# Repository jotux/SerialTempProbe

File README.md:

# SerialTempProbe
Serial temperature probe with 5 channels, K-Type thermocouples, and stm32l4 controller

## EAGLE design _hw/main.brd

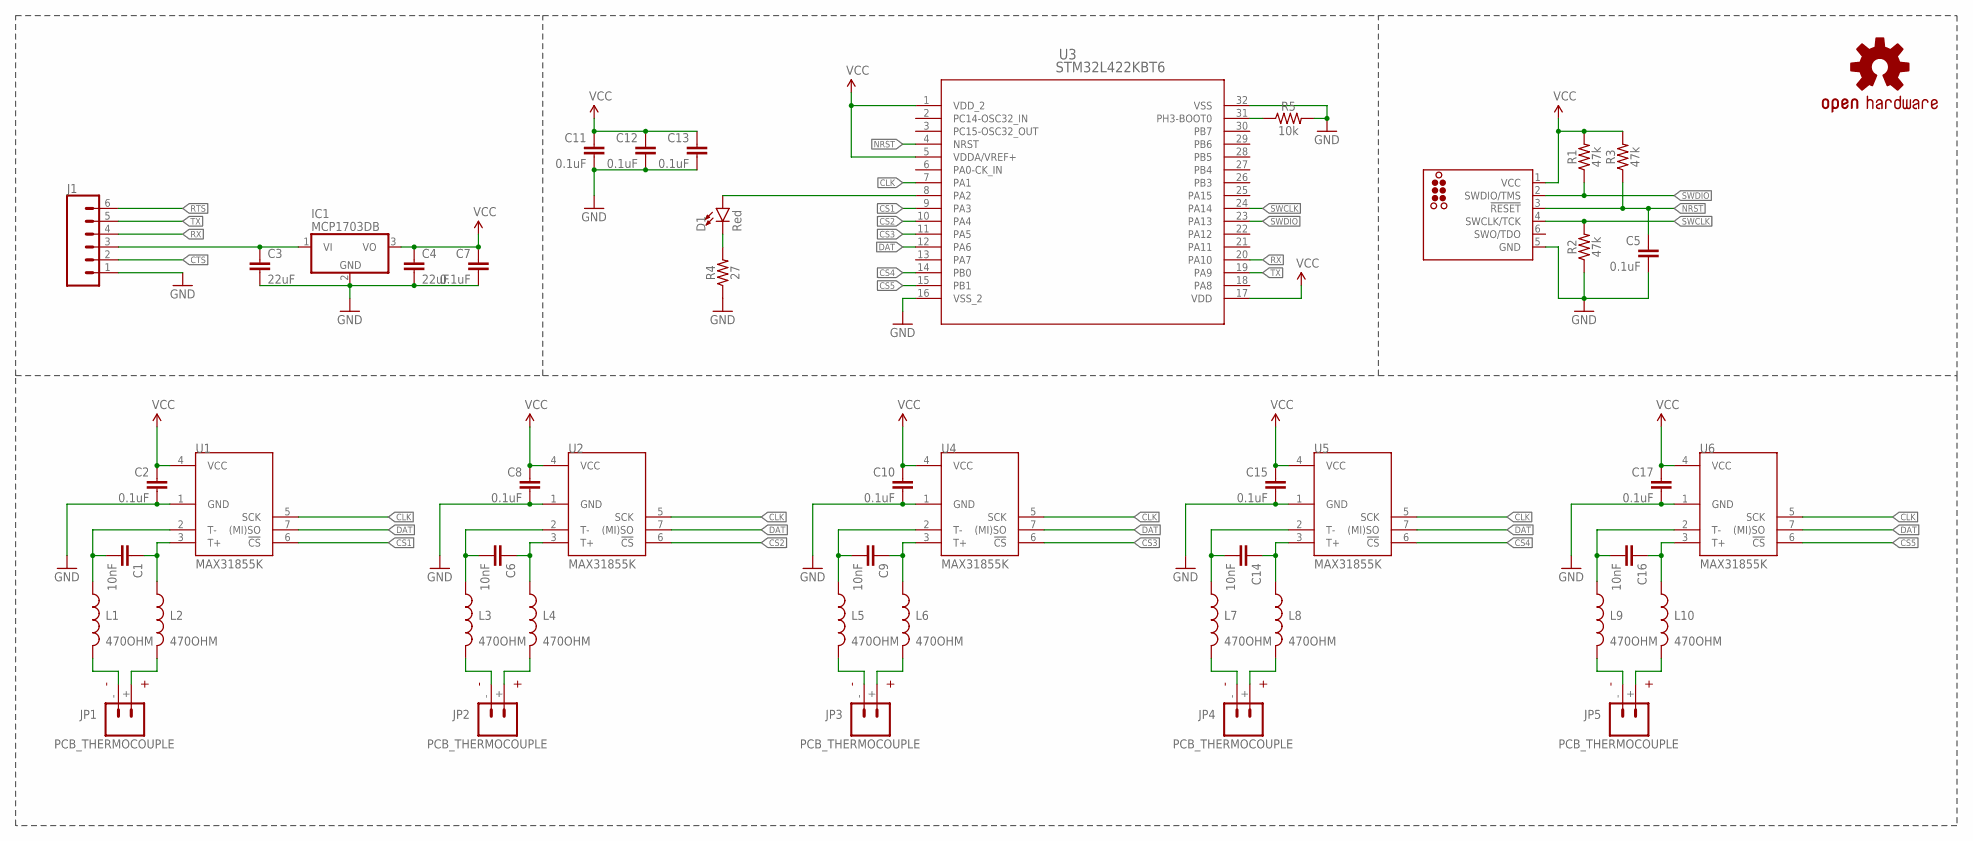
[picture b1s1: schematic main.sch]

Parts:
C1, C6, C9, C14, C16: 10nF; 0603-CAP
C2, C5, C7, C8, C10, C11, C12, C13, C15, C17: 0.1uF; 0603-CAP
C3, C4: 22uF; 0603
D1: Red; LED-0603
IC1: MCP1703DB; SOT223
J1: CONN_06NO_SILK_NO_POP; 1X06_NO_SILK
J2: TC2030_SWD-MCP-NL; TC2030-MCP-NL
JP1, JP2, JP3, JP4, JP5: PCB_THERMOCOUPLE; PCC-SMP
L1, L2, L3, L4, L5, L6, L7, L8, L9, L10: 470OHM; 0603
LOGO1: OSHW-LOGOL; OSHW-LOGO-L
R1, R2, R3: 47k; 0603
R4: 27; 0603
R5: 10k; 0603
U1, U2, U4, U5, U6: MAX31855K; SOIC8
U3: STM32L422KBT6; LQFP_422KBT6_STM

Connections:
+5V: C3.1, IC1.1 (VI), J1.3
CLK: U1.5 (SCK), U2.5 (SCK), U3.7 (PA1), U4.5 (SCK), U5.5 (SCK), U6.5 (SCK)
CS1: U1.6 (!CS), U3.9 (PA3)
CS2: U2.6 (!CS), U3.10 (PA4)
CS3: U3.11 (PA5), U4.6 (!CS)
CS4: U3.14 (PB0), U5.6 (!CS)
CS5: U3.15 (PB1), U6.6 (!CS)
CTS: J1.2
DAT: U1.7 ((MI)SO), U2.7 ((MI)SO), U3.12 (PA6), U4.7 ((MI)SO), U5.7 ((MI)SO), U6.7 ((MI)SO)
GND: C2.2, C3.2, C4.2, C5.2, C7.2, C8.2, C10.2, C11.2, C12.2, C13.2, C15.2, C17.2, IC1.2 (GND), J1.1, J2.5 (GND), R2.1, R4.1, R5.2, U1.1 (GND), U2.1 (GND), U3.16 (VSS_2), U3.32 (VSS), U4.1 (GND), U5.1 (GND), U6.1 (GND)
unnamed: C6.1, L4.1, U2.3 (T+)
unnamed: C6.2, L3.1, U2.2 (T-)
unnamed: JP2.-, L3.2
unnamed: JP2.+, L4.2
unnamed: C1.2, L1.1, U1.2 (T-)
unnamed: JP1.-, L1.2
unnamed: C1.1, L2.1, U1.3 (T+)
unnamed: C9.1, L6.1, U4.3 (T+)
unnamed: JP1.+, L2.2
unnamed: C9.2, L5.1, U4.2 (T-)
unnamed: JP3.-, L5.2
unnamed: JP3.+, L6.2
unnamed: C14.1, L8.1, U5.3 (T+)
unnamed: C14.2, L7.1, U5.2 (T-)
unnamed: JP4.-, L7.2
unnamed: JP4.+, L8.2
unnamed: C16.1, L10.1, U6.3 (T+)
unnamed: C16.2, L9.1, U6.2 (T-)
unnamed: JP5.-, L9.2
unnamed: JP5.+, L10.2
unnamed: D1.A, U3.8 (PA2)
unnamed: D1.C, R4.2
unnamed: R5.1, U3.31 (PH3-BOOT0)
NRST: C5.1, J2.3 (!RESET), R3.1, U3.4 (NRST)
RTS: J1.6
RX: J1.4, U3.20 (PA10)
SWCLK: J2.4 (SWCLK/TCK), R2.2, U3.24 (PA14)
SWDIO: J2.2 (SWDIO/TMS), R1.1, U3.23 (PA13)
TX: J1.5, U3.19 (PA9)
VCC: C2.1, C4.1, C7.1, C8.1, C10.1, C11.1, C12.1, C13.1, C15.1, C17.1, IC1.3 (VO), J2.1 (VCC), R1.2, R3.2, U1.4 (VCC), U2.4 (VCC), U3.1 (VDD_2), U3.5 (VDDA/VREF+), U3.17 (VDD), U4.4 (VCC), U5.4 (VCC), U6.4 (VCC)

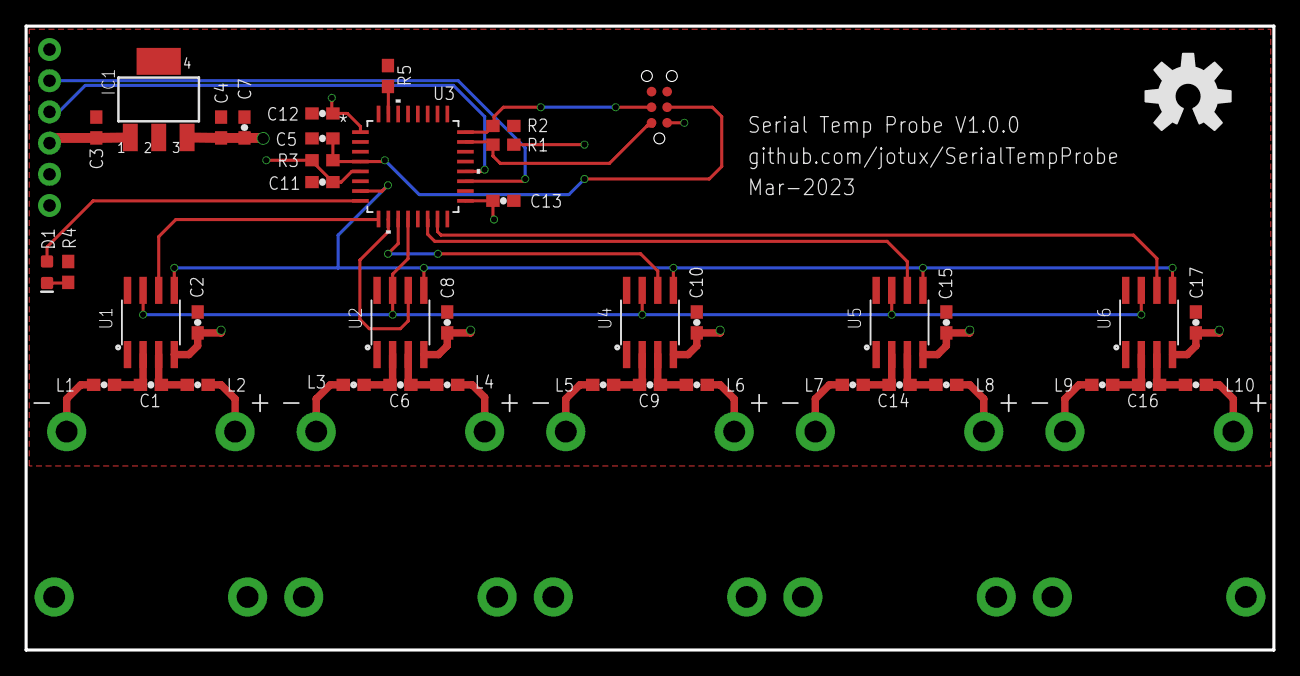
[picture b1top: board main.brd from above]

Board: 2 copper layers, 101.6 x 50.8 mm, 48 parts (0 on the bottom side), 38 nets.

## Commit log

2023-03-22 Add schematic and board.

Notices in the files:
parts and their libraries:
SparkFun-Capacitors: Licensing: Creative Commons ShareAlike 4.0 International - https://creativecommons.org/licenses/by-sa/4.0
tag-connect: ©2009 ROFA.cz - modified and updated by Robert Darlington ‹rdarlington@gmail.com›
COPYRIGHT: Copyright (C) 2023 Ultra Librarian. All rights reserved.
